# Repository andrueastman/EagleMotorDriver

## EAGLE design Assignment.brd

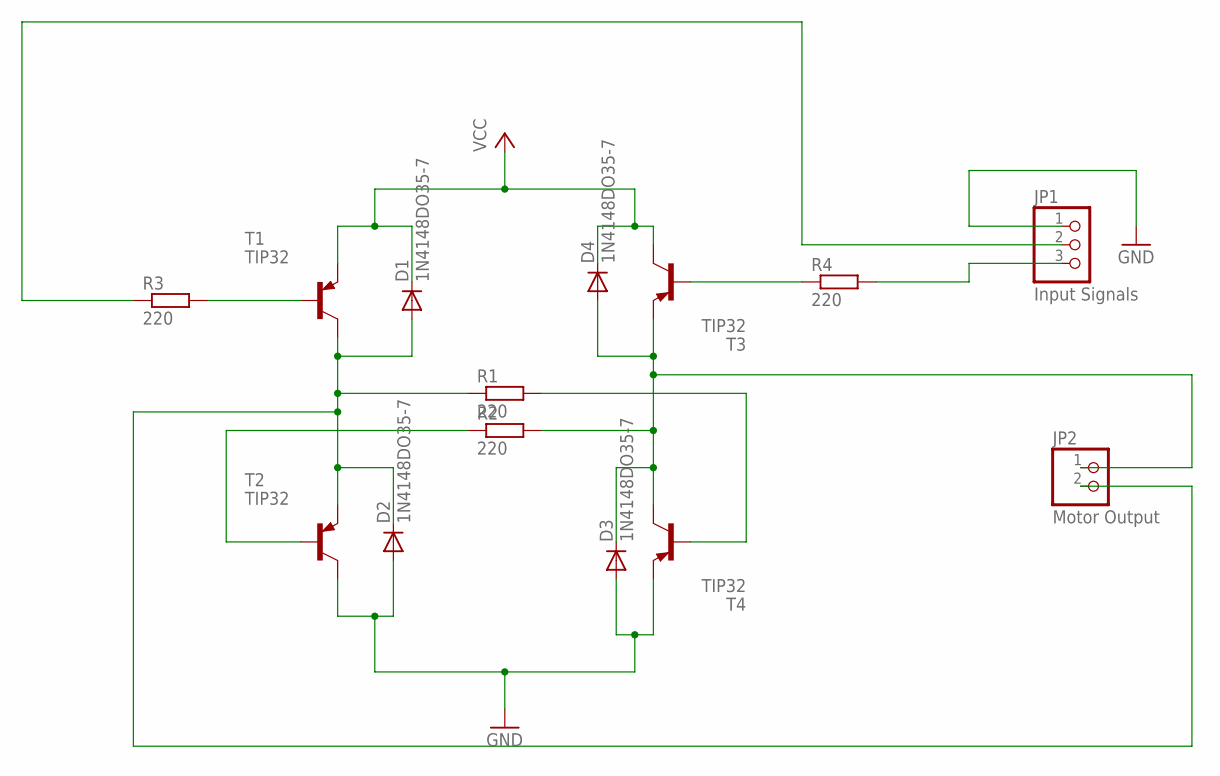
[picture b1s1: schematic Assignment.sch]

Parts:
D1, D2, D3, D4: 1N4148DO35-7; DO35-7
JP1: Input Signals; 1X03
JP2: Motor Output; 1X02
R1, R2, R3, R4: 220; 0204/7
T1, T2, T3, T4: TIP32; TO220

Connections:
GND: D2.A, D3.A, JP1.1, T2.2 (C), T4.3 (E)
unnamed: JP1.3, R4.2
unnamed: D1.A, D2.C, JP2.2, R1.1, T1.2 (C), T2.3 (E)
unnamed: D3.C, D4.A, JP2.1, R2.2, T3.3 (E), T4.2 (C)
unnamed: JP1.2, R3.1
unnamed: R4.1, T3.1 (B)
unnamed: R2.1, T2.1 (B)
unnamed: R1.2, T4.1 (B)
unnamed: R3.2, T1.1 (B)
VCC: D1.C, D4.C, T1.3 (E), T3.2 (C)

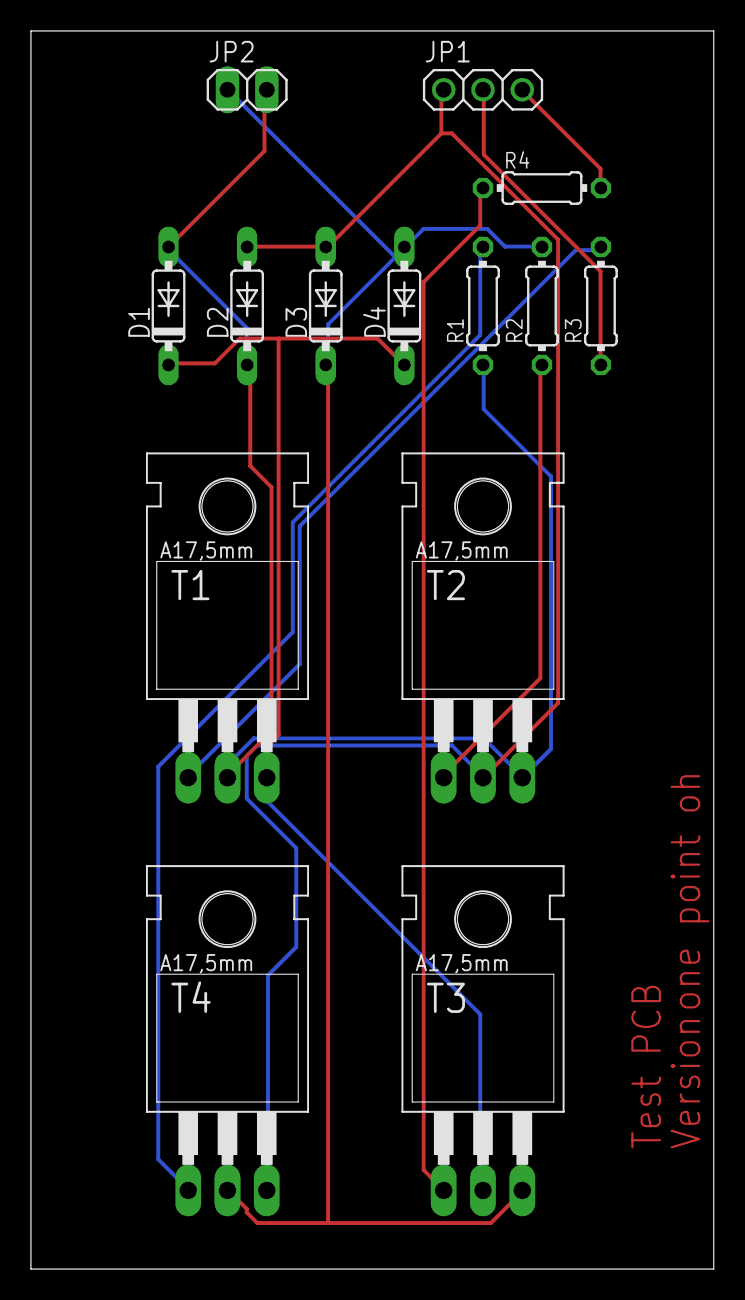
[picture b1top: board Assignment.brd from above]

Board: 2 copper layers, 44.1 x 80.0 mm, 14 parts (0 on the bottom side), 10 nets.

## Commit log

2016-08-16 My attempt at learning how to use eagle a few years ago. Backing it up now.
